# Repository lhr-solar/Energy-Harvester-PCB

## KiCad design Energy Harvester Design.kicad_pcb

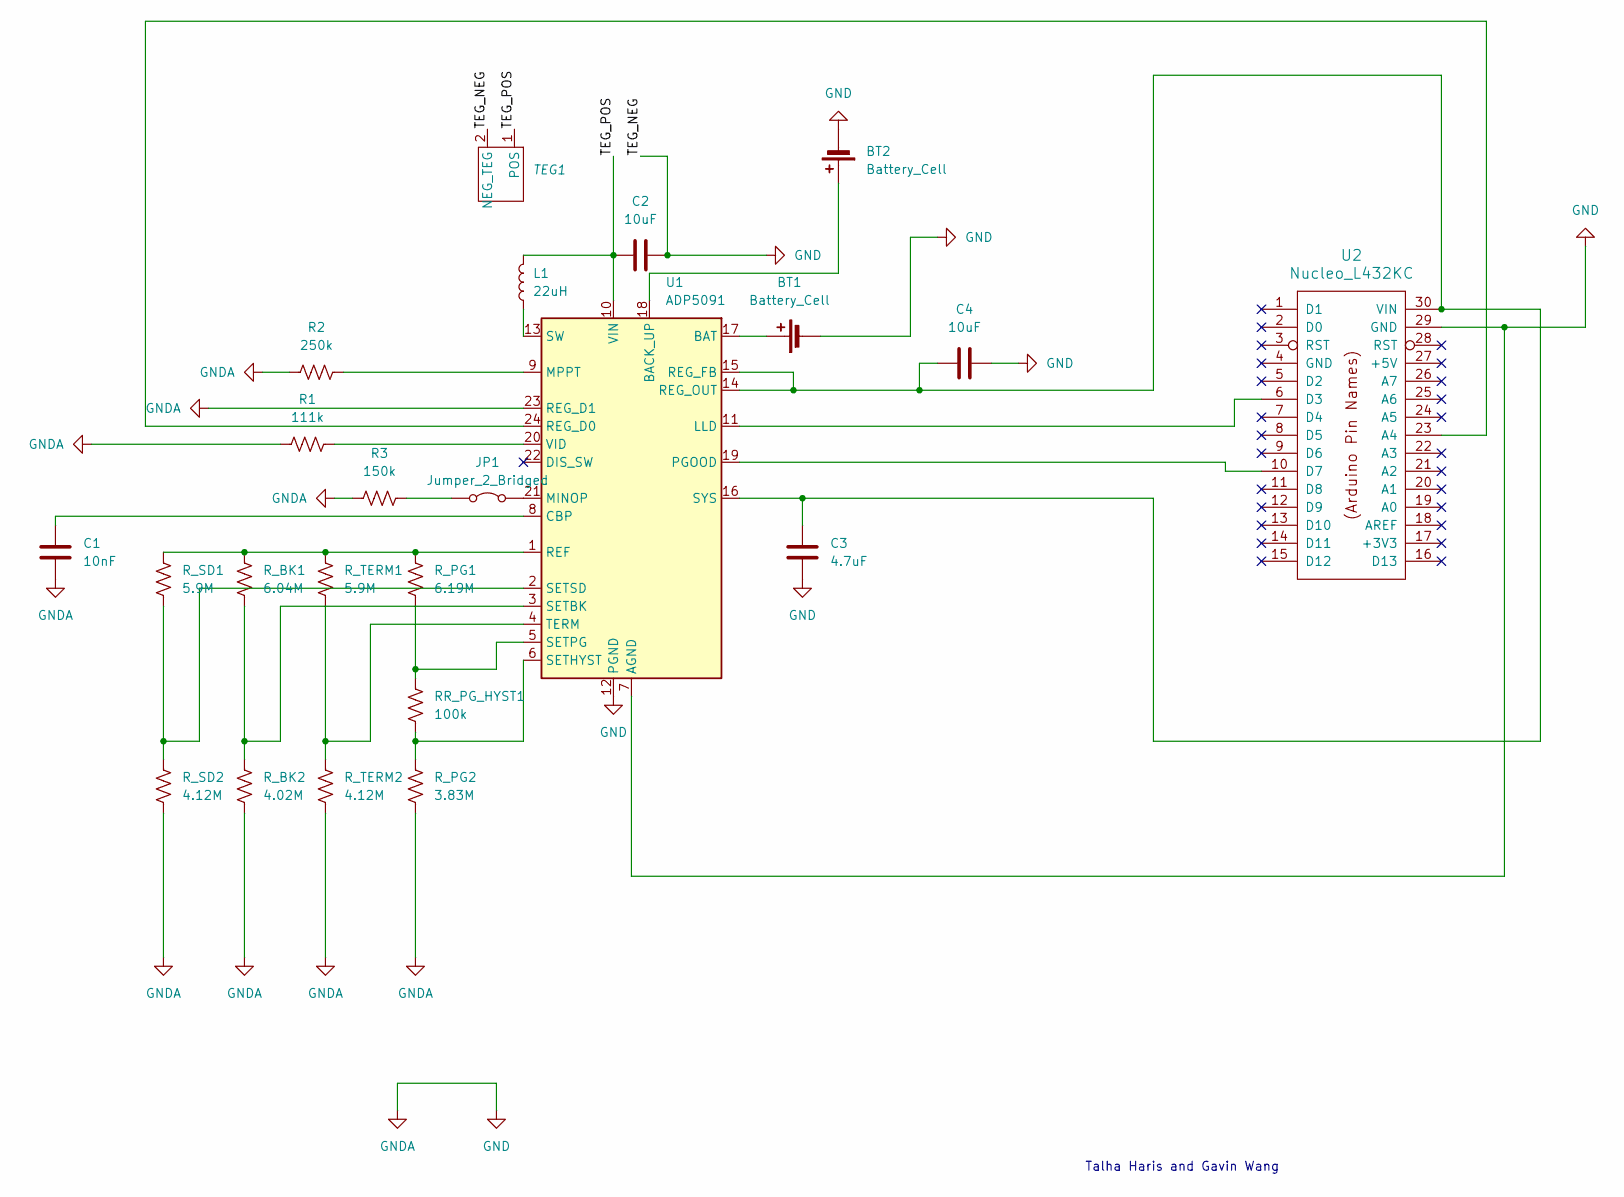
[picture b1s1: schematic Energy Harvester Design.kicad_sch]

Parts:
BT1, BT2: Battery_Cell; BatteryHolder_Keystone_103_1x20mm
C1: 10nF; C_0805_2012Metric
C2, C4: 10uF; C_0805_2012Metric
C3: 4.7uF; C_0805_2012Metric
JP1: Jumper_2_Bridged; SolderJumper-2_P1.3mm_Bridged_Pad1.0x1.5mm
L1: 22uH; L_0805_2012Metric
R1: 111k; R_0805_2012Metric
R2: 250k; R_0805_2012Metric
R3: 150k; R_0805_2012Metric
RR_PG_HYST1: 100k; R_0805_2012Metric
R_BK1: 6.04M; R_0805_2012Metric
R_BK2: 4.02M; R_0805_2012Metric
R_PG1: 6.19M; R_0805_2012Metric
R_PG2: 3.83M; R_0805_2012Metric
R_SD1: 5.9M; R_0805_2012Metric
R_SD2: 4.12M; R_0805_2012Metric
R_TERM1: 5.9M; R_0805_2012Metric
R_TERM2: 4.12M; R_0805_2012Metric
TEG1: Molex_Micro-Fit_3.0_43650-0200_1x02_P3.00mm_Horizontal
U1: ADP5091; LFCSP-24-1EP_4x4mm_P0.5mm_EP2.3x2.3mm
U2: Nucleo_L432KC; NucleoL432KC

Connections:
/TEG_POS: C2.1, L1.2, TEG1.1 (POS), U1.10 (VIN)
GND: BT1.2 (-), BT2.2 (-), C1.2, C2.2, C3.2, C4.2, R1.1, R2.1, R3.1, R_BK2.2, R_PG2.2, R_SD2.2, R_TERM2.2, TEG1.2 (NEG_TEG), U1.7 (AGND), U1.12 (PGND), U1.23 (REG_D1), U1.25 (AGND), U2.29 (GND)
unnamed: BT1.1 (+), U1.17 (BAT)
unnamed: BT2.1 (+), U1.18 (BACK_UP)
unnamed: JP1.1 (A), R3.2
unnamed: JP1.2 (B), U1.21 (MINOP)
unnamed: C1.1, U1.8 (CBP)
unnamed: U1.11 (LLD), U2.6 (D3)
unnamed: R2.2, U1.9 (MPPT)
unnamed: U1.19 (PGOOD), U2.10 (D7)
unnamed: R_BK1.1, R_PG1.1, R_SD1.1, R_TERM1.1, U1.1 (REF)
unnamed: U1.24 (REG_D0), U2.23 (A4)
unnamed: C3.1, C4.1, U1.14 (REG_OUT), U1.15 (REG_FB), U1.16 (SYS), U2.30 (VIN)
unnamed: R_BK1.2, R_BK2.1, U1.3 (SETBK)
unnamed: RR_PG_HYST1.2, R_PG2.1, U1.6 (SETHYST)
unnamed: RR_PG_HYST1.1, R_PG1.2, U1.5 (SETPG)
unnamed: R_SD1.2, R_SD2.1, U1.2 (SETSD)
unnamed: L1.1, U1.13 (SW)
unnamed: R_TERM1.2, R_TERM2.1, U1.4 (TERM)
unnamed: R1.2, U1.20 (VID)

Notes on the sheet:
Talha Haris and Gavin Wang

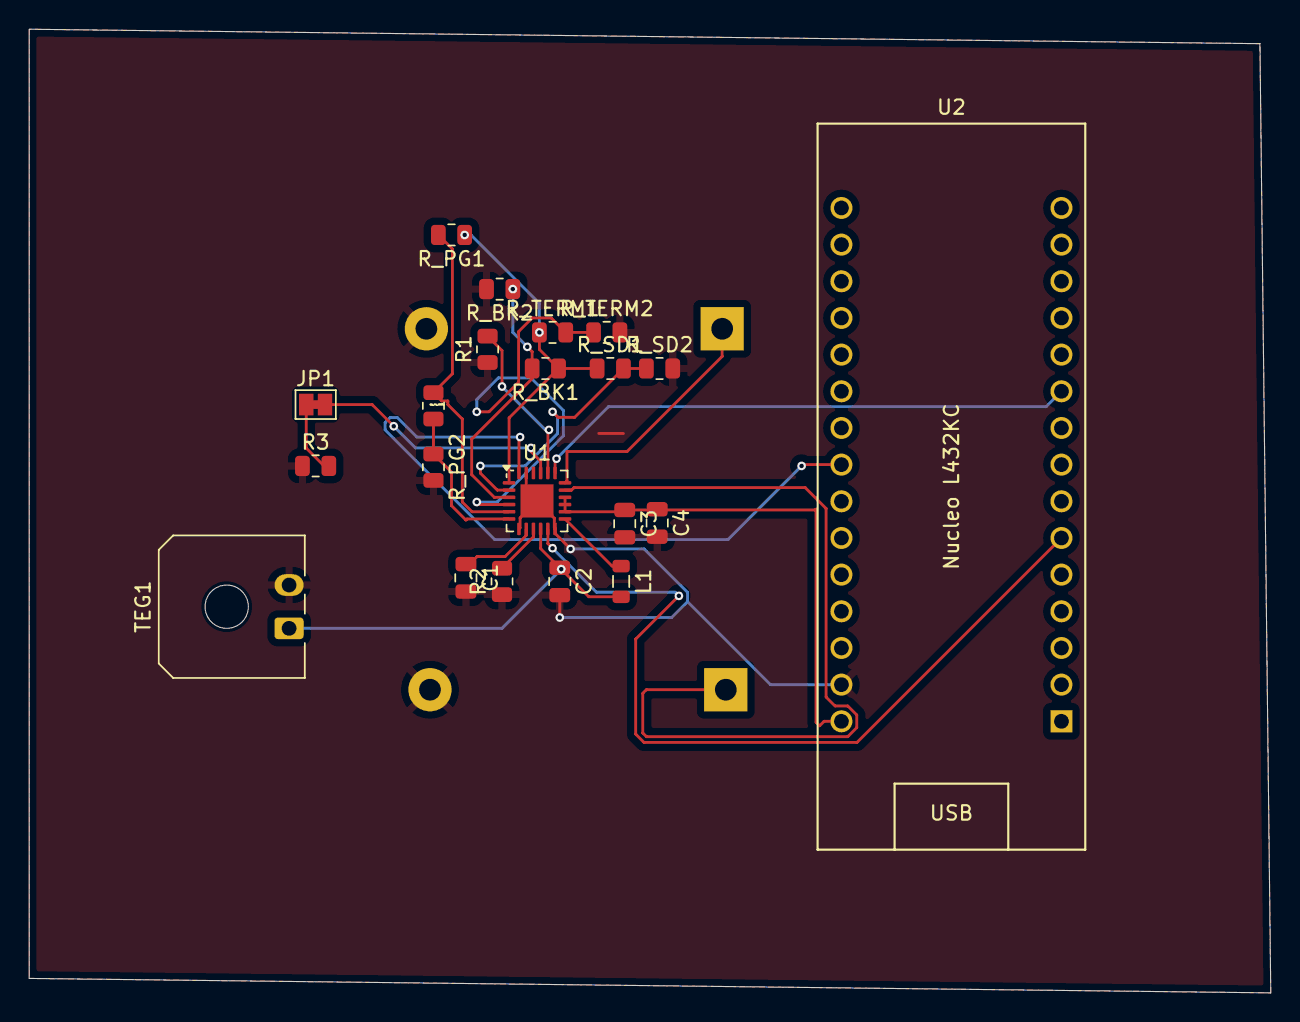
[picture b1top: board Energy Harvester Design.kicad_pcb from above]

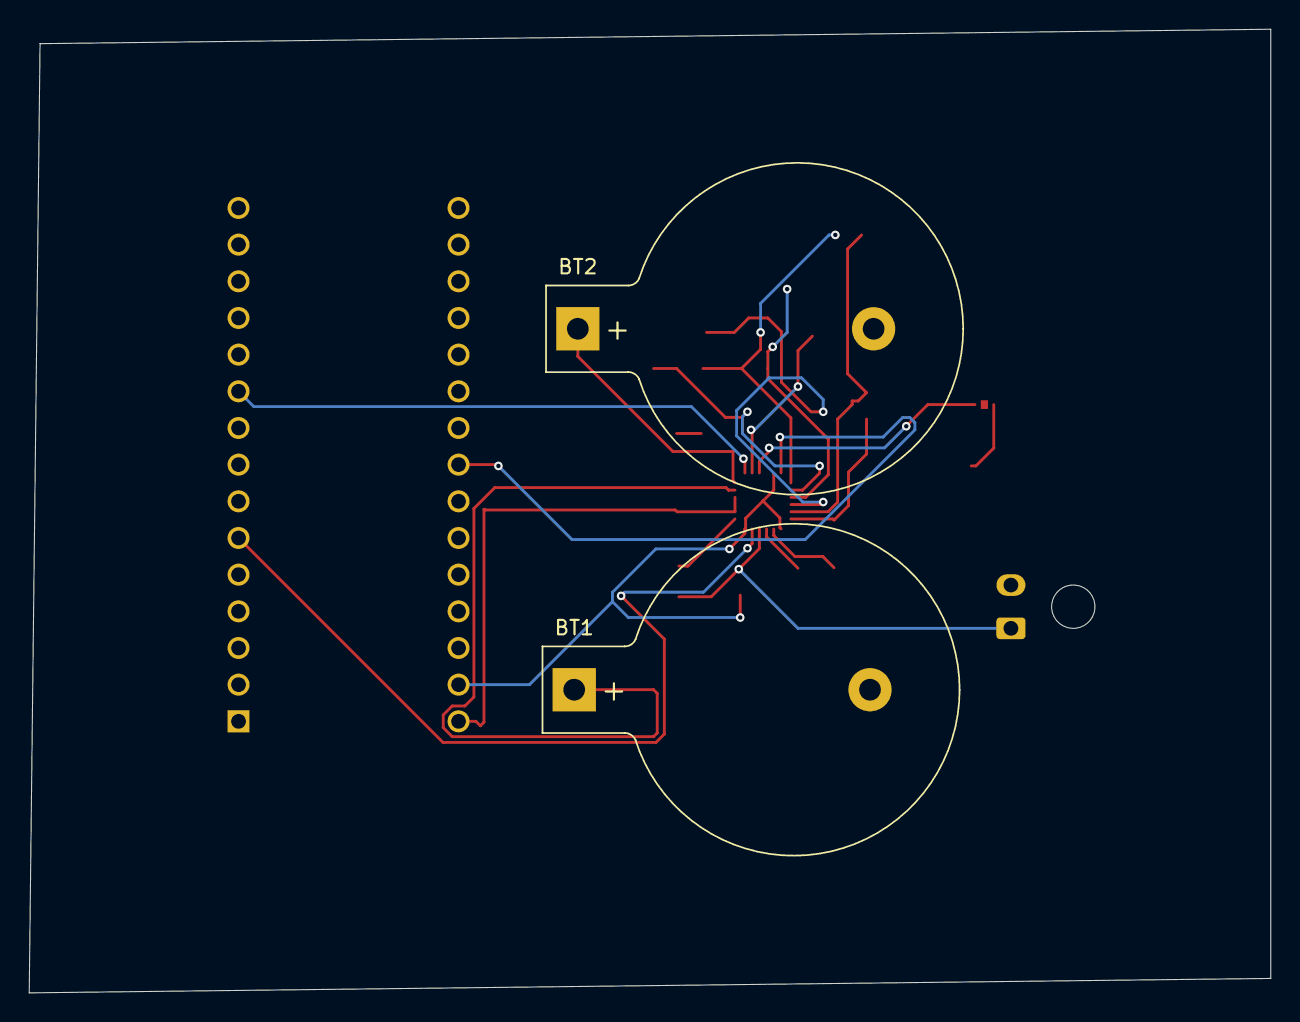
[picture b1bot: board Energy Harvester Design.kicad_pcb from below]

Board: 2 copper layers, 86.0 x 66.8 mm, 23 parts (2 on the bottom side), 20 nets.

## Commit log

2025-02-15 updated schematic
2025-02-15 Update Sch
2025-04-05 Update PCB
